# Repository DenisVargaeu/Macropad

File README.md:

# Macropad

<p align="center">

</p>

<p align="center">
  <strong>A custom 16-key macropad with OLED display and RGB LED, built around the Raspberry Pi Pico (RP2040/RP2350).</strong>
</p>

<p align="center">
  <a href="#-quick-view">Quick View</a> •
  <a href="#-features">Features</a> •
  <a href="#-hardware-specifications">Specs</a> •
  <a href="#-pinout">Pinout</a> •
  <a href="#-repository-structure">Repository</a> •
  <a href="#-getting-started">Getting Started</a> •
  <a href="#-bill-of-materials">BOM</a> •
  <a href="#-firmware">Firmware</a> •
  <a href="#-fabrication">Fabrication</a> •
  <a href="#-assembly">Assembly</a> •
  <a href="#-customization">Customization</a> •
  <a href="#-license">License</a>
</p>

---

## 📸 Quick View

| Document | Preview | Description |
|----------|---------|-------------|
| **Schematic** |  | Full schematic, all pages |
| **PCB Layout** |  | All layers (Cu, Silk, Mask, Edge) |
| **3D Model (STEP)** |  | For CAD (FreeCAD, Fusion 360, OnShape) |
| **3D Model (STL — Full)** |  | **All components** (18 MB) |
| **3D Model (STL — PCB+Pico)** |  | Board + Pico only (6 MB) — for enclosures |
| **3D Model (STL — Buttons only)** |  | Buttons only (0.4 MB) |

> 💡 **View in browser:** Click any PDF/STL link above — GitHub renders them natively. No KiCad required!

---

## ✨ Features

- **16 tactile keys** in a 4×4 matrix — direct GPIO (no matrix scanning needed)
- **0.91″ OLED display** (128×32, SSD1306, I2C) — status, layers, animations
- **RGB LED** (5 mm, common cathode) — per-key or global lighting
- **Raspberry Pi Pico / Pico 2** — RP2040 or RP2350, USB-C, BOOTSEL button accessible
- **Through-hole only** — easy hand soldering, beginner-friendly
- **Open hardware** — CERN-OHL-P-2.0 license, modify freely

---

## 🔧 Hardware Specifications

| Component | Part | Qty | Details |
|-----------|------|-----|---------|
| **MCU** | Raspberry Pi Pico / Pico 2 | 1 | RP2040 / RP2350, 133 MHz, 264 KB SRAM, 2 MB Flash |
| **Display** | ER_OLEDM0.91_1x-I2C | 1 | 0.91″, 128×32, SSD1306, I2C (EastRising/BuyDisplay) |
| **Keys** | SW_PUSH_6mm (6×6 mm tactile) | 16 | Through-hole, 4-pin (2×2 internally connected) |
| **RGB LED** | LED_D5.0mm-4_RGB_Wide_Pins | 1 | 5 mm, 4-pin common cathode (Kingbright WP154A4) |
| **Resistors** | 1/4 W axial (220–330 Ω) | 3 | Current limiting for R/G/B channels |
| **PCB** | Custom 2-layer | 1 | 1.6 mm FR4, ENIG/HASL, 100×60 mm approx. |

---

## 📌 Pinout

### Buttons — Direct GPIO (4×4 Grid)

| Key | Position | GPIO | Switch Ref | Net Name |
|-----|----------|------|------------|----------|
| 1 | Top-Left | GPIO0 | SW16 | `Net-(A1-GPIO0)` |
| 2 | | GPIO1 | SW15 | `Net-(A1-GPIO1)` |
| 3 | | GPIO2 | SW14 | `Net-(A1-GPIO2)` |
| 4 | Top-Right | GPIO3 | SW13 | `Net-(A1-GPIO3)` |
| 5 | | GPIO4 | SW8 | `Net-(A1-GPIO4)` |
| 6 | | GPIO5 | SW7 | `Net-(A1-GPIO5)` |
| 7 | | GPIO6 | SW6 | `Net-(A1-GPIO6)` |
| 8 | | GPIO7 | SW5 | `Net-(A1-GPIO7)` |
| 9 | | GPIO8 | SW4 | `Net-(A1-GPIO8)` |
| 10 | | GPIO9 | SW3 | `Net-(A1-GPIO9)` |
| 11 | | GPIO10 | SW2 | `Net-(A1-GPIO10)` |
| 12 | | GPIO11 | SW1 | `Net-(A1-GPIO11)` |
| 13 | Bottom-Left | GPIO16 | SW9 | `Net-(A1-GPIO16)` |
| 14 | | GPIO17 | SW10 | `Net-(A1-GPIO17)` |
| 15 | | GPIO18 | SW11 | `Net-(A1-GPIO18)` |
| 16 | Bottom-Right | GPIO19 | SW12 | `Net-(A1-GPIO19)` |

> **Each switch:** GPIO → GND when pressed. **Enable internal pull-ups** in firmware (`Pin.PULL_UP`).

### OLED Display (I2C)

| Signal | GPIO | Display Pin | Net |
|--------|------|-------------|-----|
| SCL | GPIO15 | Pin 3 | `Net-(A1-GPIO15)` |
| SDA | GPIO14 | Pin 4 | `Net-(A1-GPIO14)` |
| VCC | 3V3 | Pin 2 | `VCC` |
| GND | GND | Pin 1 | `GND` |

### RGB LED (Common Cathode)

| Color | Anode Net | Resistor | MCU GPIO |
|-------|-----------|----------|----------|
| **Blue** | `Net-(D2-BA)` | R1 | GPIO20 |
| **Green** | `Net-(D2-GA)` | R2 | GPIO21 |
| **Red** | `Net-(D2-RA)` | R3 | GPIO22 |
| **Cathode** | GND | — | — |

> **Resistor values:** 220 Ω (≈10 mA @ 3.3 V) or 330 Ω (≈7 mA). Adjust for brightness/uniformity.

---

## 📁 Repository Structure

```
macropad/
├── 📋 KiCad Source (editable)
│   ├── macropad.kicad_pro          # Project file
│   ├── macropad.kicad_sch          # Schematic
│   ├── macropad.kicad_pcb          # PCB layout
│   └── macropad.kicad_prl          # Local settings
│
├── 📄 Documentation (view anywhere)
│   ├── macropad-schematic.pdf      # Full schematic (PDF)
│   └── macropad-pcb.pdf            # PCB all layers (PDF)
│
├── 🎯 3D Models
│   ├── macropad-3d.step            # STEP — for CAD (FreeCAD, Fusion 360)
│   ├── macropad-3d-full.stl        # STL — ALL components (18 MB)
│   ├── macropad-pcb-pico.stl       # STL — PCB + Pico only (6 MB)
│   └── macropad-3d.stl             # STL — buttons only (0.4 MB)
│
├── 🏭 Fabrication
│   └── gerbers/                    # Gerber + drill files (gitignored)
│
├── 🔧 Utilities
│   └── export_stl.py               # FreeCAD script for STL export
│
├── 📜 LICENSE                      # CERN-OHL-P-2.0
└── 📖 README.md                    # This file
```

### Files by Category

| Category | Files | Purpose |
|----------|-------|---------|
| **KiCad Source** | `.kicad_pro`, `.kicad_sch`, `.kicad_pcb`, `.kicad_prl` | Full editable design — open in KiCad 10+ |
| **Documentation** | `macropad-schematic.pdf`, `macropad-pcb.pdf` | View schematic/PCB without KiCad |
| **3D Models** | `.step`, `.stl` (3 variants) | CAD, 3D printing, enclosure design |
| **Fabrication** | `gerbers/` (generated) | Send to PCB manufacturer |
| **License** | `LICENSE` | CERN-OHL-P-2.0 (permissive open hardware) |

---

## 🚀 Getting Started

### Prerequisites

- **KiCad 10.0+** — [Download](https://www.kicad.org/download/)
- **Raspberry Pi Pico SDK** — for C/C++ firmware
- **Soldering iron, solder, flux** — through-hole components
- **Female headers (2×20)** — for Pico module (or solder directly)

### Opening the Project

```bash
git clone https://github.com/DenisVargaeu/Macropad.git
cd Macropad
# Open in KiCad
open macropad.kicad_pro    # macOS
xdg-open macropad.kicad_pro  # Linux
start macropad.kicad_pro     # Windows
```

> **All KiCad source files are included.** No need to re-create anything — just open and edit.

---

## 📦 Bill of Materials (BOM)

| Qty | Ref | Part | Value / Spec | Notes |
|-----|-----|------|--------------|-------|
| 1 | A1 | Raspberry Pi Pico / Pico 2 | RP2040 / RP2350 | With headers or castellated |
| 1 | U1 | ER_OLEDM0.91_1x-I2C | 128×32, SSD1306, I2C | EastRising / BuyDisplay |
| 16 | SW1–SW16 | Tactile switch 6×6 mm | SW_PUSH_6mm | 4-pin, through-hole |
| 1 | D2 | RGB LED 5 mm | Common cathode, 4-pin | Kingbright WP154A4 or compatible |
| 3 | R1, R2, R3 | Resistor 1/4 W axial | 220–330 Ω | Current limiting (R/G/B) |
| 1 | — | PCB | Custom, 2-layer | Order from Gerbers |

**Approximate cost (per unit, qty 1):** ~$15–25 USD (Pico + display + switches + PCB)

---

## 🏭 Fabrication

### Option A: Use Pre-generated Gerbers (Recommended)

The `gerbers/` directory contains production-ready files:

```
gerbers/
├── macropad-F_Cu.gtl        # Front copper
├── macropad-B_Cu.gbl        # Back copper
├── macropad-F_Silkscreen.gto # Front silkscreen
├── macropad-B_Silkscreen.gbo # Back silkscreen
├── macropad-F_Mask.gts       # Front soldermask
├── macropad-B_Mask.gbs       # Back soldermask
├── macropad-Edge_Cuts.gm1    # Board outline
└── macropad.drl              # Drill file
```

Upload to **JLCPCB, PCBWay, OSH Park, AISLER**, etc.

### Option B: Generate from KiCad

1. Open `macropad.kicad_pro` in KiCad
2. `File → Fabrication Outputs → Gerbers (.gbr)`
   - Layers: F.Cu, B.Cu, F.SilkS, B.SilkS, F.Mask, B.Mask, Edge.Cuts
   - Format: Gerber X2, mm, 4.6
3. `File → Fabrication Outputs → Drill Files (.drl)`
   - Format: Excellon, mm, PTH+NPTH
4. Zip and send to fab

### Board Specifications

| Parameter | Value |
|-----------|-------|
| Layers | 2 |
| Thickness | 1.6 mm |
| Material | FR4 (standard) |
| Copper weight | 1 oz (35 µm) |
| Min track/space | 0.15 mm / 0.15 mm (6/6 mil) |
| Min drill | 0.3 mm (12 mil) |
| Surface finish | HASL or ENIG |
| Soldermask | Green (standard) |
| Silkscreen | White |

---

## 🔨 Assembly

### Component Placement

All components are **through-hole** except the Pico (castellated pads).

### Recommended Soldering Order

| Step | Components | Tips |
|------|------------|------|
| 1 | **Resistors** (R1, R2, R3) | Lowest profile first |
| 2 | **Tactile switches** (SW1–SW16) | Snap in, solder one pin, align, solder rest |
| 3 | **RGB LED** (D2) | Pin 1 = Blue anode (square pad on silkscreen) |
| 4 | **OLED display** (U1) | Pin 1 = GND (square pad); use socket if desired |
| 5 | **Female headers** for Pico | 2×20 pin, 2.54 mm pitch |
| 6 | **Insert Pico module** | Align USB-C with board cutout |

### Orientation Notes

- **Switches:** 4 pins, internally connected in pairs — orientation doesn't matter electrically
- **RGB LED:** Pin 1 (Blue) marked on silkscreen; cathode is longest pin
- **OLED:** Pin 1 = GND (square pad on footprint)
- **Pico:** USB-C faces board edge; BOOTSEL button accessible

---

## 💻 Firmware

This repository contains **hardware only**. Firmware examples below.

### Supported Frameworks

| Framework | Language | Status | Link |
|-----------|----------|--------|------|
| **Pico SDK** | C/C++ | ✅ Native | [pico-sdk](https://github.com/raspberrypi/pico-sdk) |
| **CircuitPython** | Python | ✅ Easy | [circuitpython.org](https://circuitpython.org/board/raspberry_pi_pico/) |
| **MicroPython** | Python | ✅ Official | [micropython.org](https://micropython.org/download/rp2-pico/) |
| **KMK** | Python | ✅ Keyboard-focused | [kmkfw.io](https://kmkfw.io/) |
| **QMK** | C | ✅ Community port | [qmk.fm](https://qmk.fm/) |
| **ZMK** | C/Zephyr | ⚠️ Advanced | [zmk.dev](https://zmk.dev/) |

### Minimal CircuitPython Example

```python
# macropad_firmware.py — copy to CIRCUITPY drive
import board
import digitalio
import busio
import adafruit_ssd1306
import neopixel

# ── Buttons (16 direct GPIOs with pull-ups) ──────────────────────
key_pins = [getattr(board, f"GP{i}") for i in list(range(12)) + list(range(16, 20))]
keys = [digitalio.DigitalInOut(pin) for pin in key_pins]
for k in keys:
    k.direction = digitalio.Direction.INPUT
    k.pull = digitalio.Pull.UP

# ── OLED (I2C on GP14/GP15) ──────────────────────────────────────
i2c = busio.I2C(board.GP15, board.GP14)
display = adafruit_ssd1306.SSD1306_I2C(128, 32, i2c)
display.fill(0)
display.text("Macropad Ready", 0, 0, 1)
display.show()

# ── RGB LED (PWM on GP20/21/22) ─────────────────────────────────
# Note: Requires 3 PWM channels for color mixing
import pwmio
red_pwm = pwmio.PWMOut(board.GP22, frequency=1000, duty_cycle=0)
grn_pwm = pwmio.PWMOut(board.GP21, frequency=1000, duty_cycle=0)
blu_pwm = pwmio.PWMOut(board.GP20, frequency=1000, duty_cycle=0)

def set_color(r, g, b):
    red_pwm.duty_cycle = int(r * 65535)
    grn_pwm.duty_cycle = int(g * 65535)
    blu_pwm.duty_cycle = int(b * 65535)

# ── Main loop ─────────────────────────────────────────────────────
while True:
    for i, k in enumerate(keys):
        if not k.value:  # Pressed (active low)
            print(f"Key {i+1} pressed")
            set_color(1, 0, 0)  # Red on press
        else:
            set_color(0, 0, 0)  # Off
```

### Pico SDK (C) — Button Scan Skeleton

```c
// main.c
#include "pico/stdlib.h"
#include "hardware/i2c.h"
#include "hardware/pwm.h"

#define I2C_PORT i2c1
#define SDA_PIN 14
#define SCL_PIN 15

// Button GPIOs in order
const uint btn_gpios[] = {0,1,2,3,4,5,6,7,8,9,10,11,16,17,18,19};
const uint NUM_BTNS = 16;

// RGB PWM pins
const uint RED_PIN = 22, GRN_PIN = 21, BLU_PIN = 20;

int main() {
    stdio_init_all();

    // Buttons with pull-ups
    for (int i = 0; i < NUM_BTNS; i++) {
        gpio_init(btn_gpios[i]);
        gpio_set_dir(btn_gpios[i], GPIO_IN);
        gpio_pull_up(btn_gpios[i]);
    }

    // I2C for OLED
    i2c_init(I2C_PORT, 400000);
    gpio_set_function(SDA_PIN, GPIO_FUNC_I2C);
    gpio_set_function(SCL_PIN, GPIO_FUNC_I2C);
    gpio_pull_up(SDA_PIN); gpio_pull_up(SCL_PIN);

    // PWM for RGB
    for (uint pin : {RED_PIN, GRN_PIN, BLU_PIN}) {
        gpio_set_function(pin, GPIO_FUNC_PWM);
        uint slice = pwm_gpio_to_slice_num(pin);
        pwm_set_wrap(slice, 255);
        pwm_set_enabled(slice, true);
    }

    while (true) {
        for (int i = 0; i < NUM_BTNS; i++) {
            if (!gpio_get(btn_gpios[i])) {
                printf("Key %d pressed\n", i+1);
                pwm_set_gpio_level(RED_PIN, 255);
            } else {
                pwm_set_gpio_level(RED_PIN, 0);
            }
        }
        sleep_ms(10);
    }
}
```

### KMK (Python Keyboard Firmware)

```python
# kmk_config.py
import board
from kmk.keys import KC
from kmk.kmk_keyboard import KMKKeyboard
from kmk.scanners import DiodeOrientation
from kmk.modules.rgb import RGB

keyboard = KMKKeyboard()

# Direct pin matrix (no diodes needed with pull-ups)
keyboard.col_pins = (
    board.GP0, board.GP1, board.GP2, board.GP3,
    board.GP4, board.GP5, board.GP6, board.GP7,
    board.GP8, board.GP9, board.GP10, board.GP11,
    board.GP16, board.GP17, board.GP18, board.GP19,
)
keyboard.row_pins = (board.GND,)  # Single row to GND
keyboard.diode_orientation = DiodeOrientation.COL2ROW

# RGB on GP20/21/22
rgb = RGB(pixel_pin=board.GP20, num_pixels=1, val_default=50)
keyboard.modules.append(rgb)

# Keymap
keyboard.keymap = [
    [KC.N1, KC.N2, KC.N3, KC.N4,
     KC.N5, KC.N6, KC.N7, KC.N8,
     KC.N9, KC.A, KC.B, KC.C,
     KC.D, KC.E, KC.F, KC.G]
]

if __name__ == '__main__':
    keyboard.go()
```

---

## 🎨 Customization

| Change | How |
|--------|-----|
| **Key layout** | Edit switch positions in `macropad.kicad_pcb` (Footprint Properties → Position) |
| **Display** | Replace `Display:ER_OLEDM0.91_1x-I2C` footprint with any I2C OLED (SSD1306, SH1106) |
| **RGB LED** | Swap `LED_THT:LED_D5.0mm-4_RGB_Wide_Pins` for common-anode or different package |
| **MCU** | Footprint `Module:RaspberryPi_Pico_Common_Unspecified` supports Pico, Pico W, Pico 2 |
| **Add per-key LEDs** | Add 16× SK6812MINI-E or WS2812B footprints + series resistors |
| **Rotary encoder** | Add EC11 footprint + 2 GPIOs (e.g., GP26/GP27) |

---

## 🐛 Known Issues / Errata

| Issue | Status | Workaround |
|-------|--------|------------|
| OLED 3D model missing in KiCad library | ⚠️ Known | STL/STEP exports show placeholder; download model from BuyDisplay |
| Pico USB-C cutout may need filing | ⚠️ Minor | Test fit before soldering headers |
| RGB LED pins tight for 5 mm wide-pin | ⚠️ Minor | Slightly bend leads or use standard 2.54 mm spacing LED |

---

## 📝 Changelog

| Version | Date | Changes |
|---------|------|---------|
| **v1.0.0** | 2026-11-08 | Initial release — schematic, PCB, 3D models, documentation |

---

## 🤝 Contributing

1. Fork the repository
2. Create a feature branch: `git checkout -b feature/amazing-idea`
3. Make changes in **KiCad 10+**
4. Run DRC: `Inspect → Design Rules Checker` (must pass with 0 errors)
5. Update README if needed
6. Submit PR with clear description and screenshots

### Development Setup

```bash
# Install KiCad 10+ (Ubuntu/Debian)
sudo add-apt-repository ppa:kicad/kicad-10.0-releases
sudo apt update && sudo apt install kicad

# Or download from kicad.org
```

---

## 📚 Resources

- **Raspberry Pi Pico Datasheet** — <https://datasheets.raspberrypi.com/pico/pico-datasheet.pdf>
- **Pico 2 (RP2350) Datasheet** — <https://datasheets.raspberrypi.com/pico/pico-2-datasheet.pdf>
- **SSD1306 OLED (ER-OLEDM0.91-1)** — <https://www.buydisplay.com/download/manual/ER-OLEDM0.91-1_Datasheet.pdf>
- **Kingbright WP154A4 RGB LED** — <https://www.kingbright.com/attachments/file/psearch/000/00/00/L-154A4SUREQBFZGEW(Ver.11A).pdf>
- **KiCad 10 Documentation** — <https://docs.kicad.org/10.0/>
- **Pico SDK** — <https://github.com/raspberrypi/pico-sdk>
- **CircuitPython for Pico** — <https://circuitpython.org/board/raspberry_pi_pico/>

---

## ⚖️ License

This hardware design is released under the **CERN Open Hardware Licence Version 2 - Permissive (CERN-OHL-P-2.0)**.

```
Copyright (c) 2026 Denis Varga

Licensed under the CERN-OHL-P-2.0 or any later version.
You may redistribute and modify this design under the terms of the CERN-OHL-P-2.0.
This design is distributed WITHOUT ANY EXPRESS OR IMPLIED WARRANTY.
See the CERN-OHL-P-2.0 for details.
```

**SPDX-License-Identifier:** `CERN-OHL-P-2.0`

Full license text: <https://ohwr.org/cern_ohl_p_2_0.txt> | <https://opensource.org/licenses/CERN-OHL-P-2.0>

---

<p align="center">
  <strong>Designed with ❤️ in KiCad 10.0</strong><br>
  Made for makers, by makers
</p>

<p align="center">
  <a href="https://github.com/DenisVargaeu/Macropad">⭐ Star this repo</a> •
  <a href="https://github.com/DenisVargaeu/Macropad/issues">🐛 Report bug</a> •
  <a href="https://github.com/DenisVargaeu/Macropad/discussions">💬 Discuss</a>
</p>

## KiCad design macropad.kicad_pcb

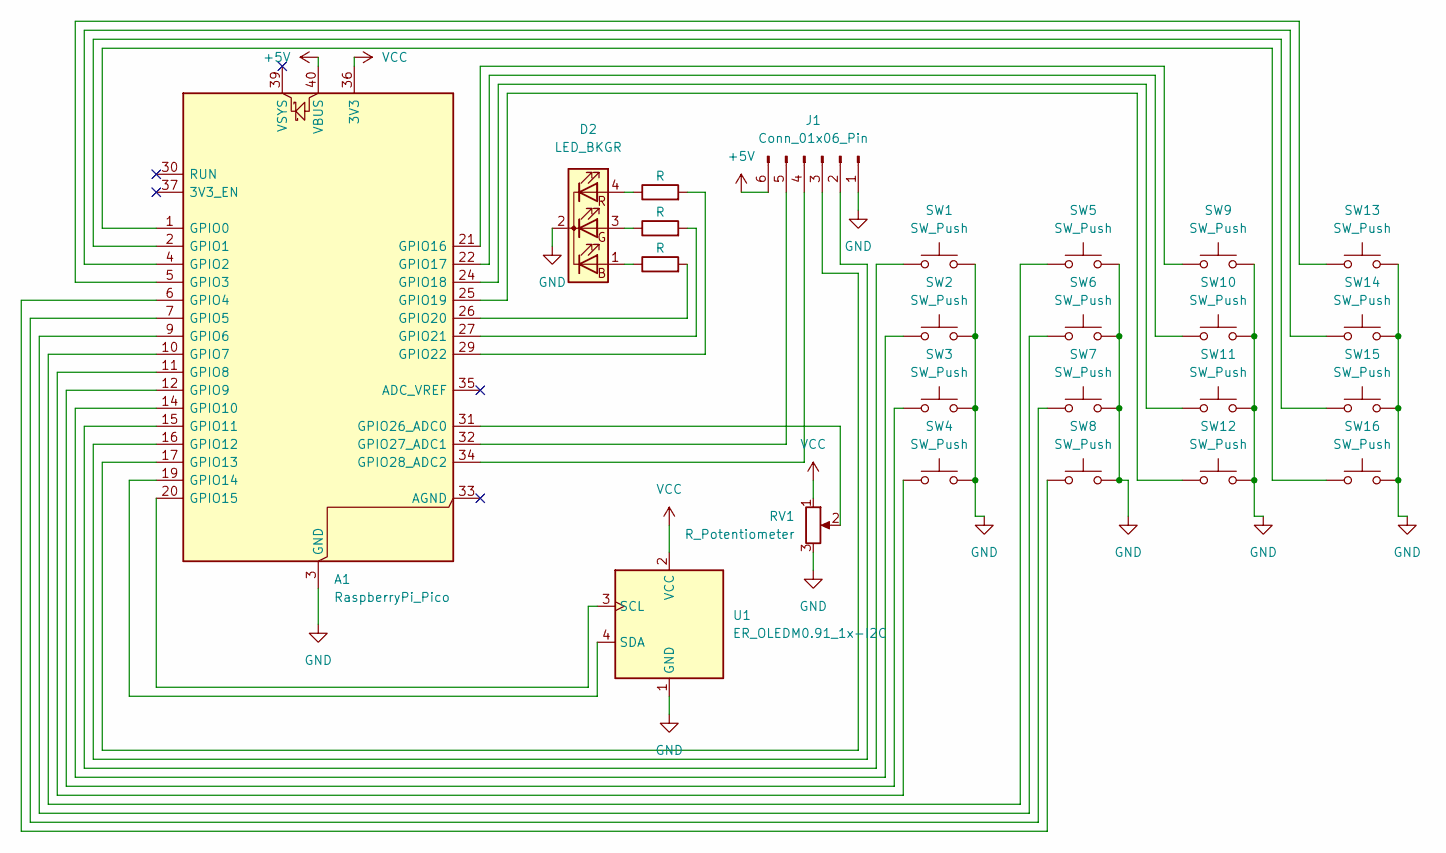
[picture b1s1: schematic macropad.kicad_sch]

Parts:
A1: RaspberryPi_Pico; RaspberryPi_Pico_Common_Unspecified
D2: LED_BKGR; LED_D5.0mm-4_RGB_Wide_Pins
J1: Conn_01x06_Pin
R1, R2, R3: R; R_Axial_DIN0207_L6.3mm_D2.5mm_P7.62mm_Horizontal
RV1: R_Potentiometer; Potentiometer_Alps_RK09K_Single_Vertical
SW1, SW2, SW3, SW4, SW5, SW6, SW7, SW8, SW9, SW10, SW11, SW12, SW13, SW14, SW15, SW16: SW_Push; SW_PUSH_6mm
U1: ER_OLEDM0.91_1x-I2C

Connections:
+5V: A1.40 (VBUS), J1.6
GND: A1.3 (GND), A1.8 (GND), A1.13 (GND), A1.18 (GND), A1.23 (GND), A1.28 (GND), A1.38 (GND), D2.2 (K), J1.1, RV1.3, SW1.2, SW2.2, SW3.2, SW4.2, SW5.2, SW6.2, SW7.2, SW8.2, SW9.2, SW10.2, SW11.2, SW12.2, SW13.2, SW14.2, SW15.2, SW16.2, U1.1 (GND)
unnamed: A1.1 (GPIO0), SW16.1
unnamed: A1.2 (GPIO1), SW15.1
unnamed: A1.4 (GPIO2), SW14.1
unnamed: A1.5 (GPIO3), SW13.1
unnamed: A1.6 (GPIO4), SW8.1
unnamed: A1.7 (GPIO5), SW7.1
unnamed: A1.9 (GPIO6), SW6.1
unnamed: A1.10 (GPIO7), SW5.1
unnamed: A1.11 (GPIO8), SW4.1
unnamed: A1.12 (GPIO9), SW3.1
unnamed: A1.14 (GPIO10), SW2.1
unnamed: A1.15 (GPIO11), SW1.1
unnamed: A1.16 (GPIO12), J1.2
unnamed: A1.17 (GPIO13), J1.3
unnamed: A1.19 (GPIO14), U1.4 (SDA)
unnamed: A1.20 (GPIO15), U1.3 (SCL)
unnamed: A1.21 (GPIO16), SW9.1
unnamed: A1.22 (GPIO17), SW10.1
unnamed: A1.24 (GPIO18), SW11.1
unnamed: A1.25 (GPIO19), SW12.1
unnamed: A1.26 (GPIO20), R1.2
unnamed: A1.27 (GPIO21), R2.2
unnamed: A1.29 (GPIO22), R3.2
unnamed: A1.31 (GPIO26_ADC0), RV1.2
unnamed: A1.32 (GPIO27_ADC1), J1.5
unnamed: A1.34 (GPIO28_ADC2), J1.4
unnamed: D2.1 (BA), R1.1
unnamed: D2.3 (GA), R2.1
unnamed: D2.4 (RA), R3.1
VCC: A1.36 (3V3), RV1.1, U1.2 (VCC)

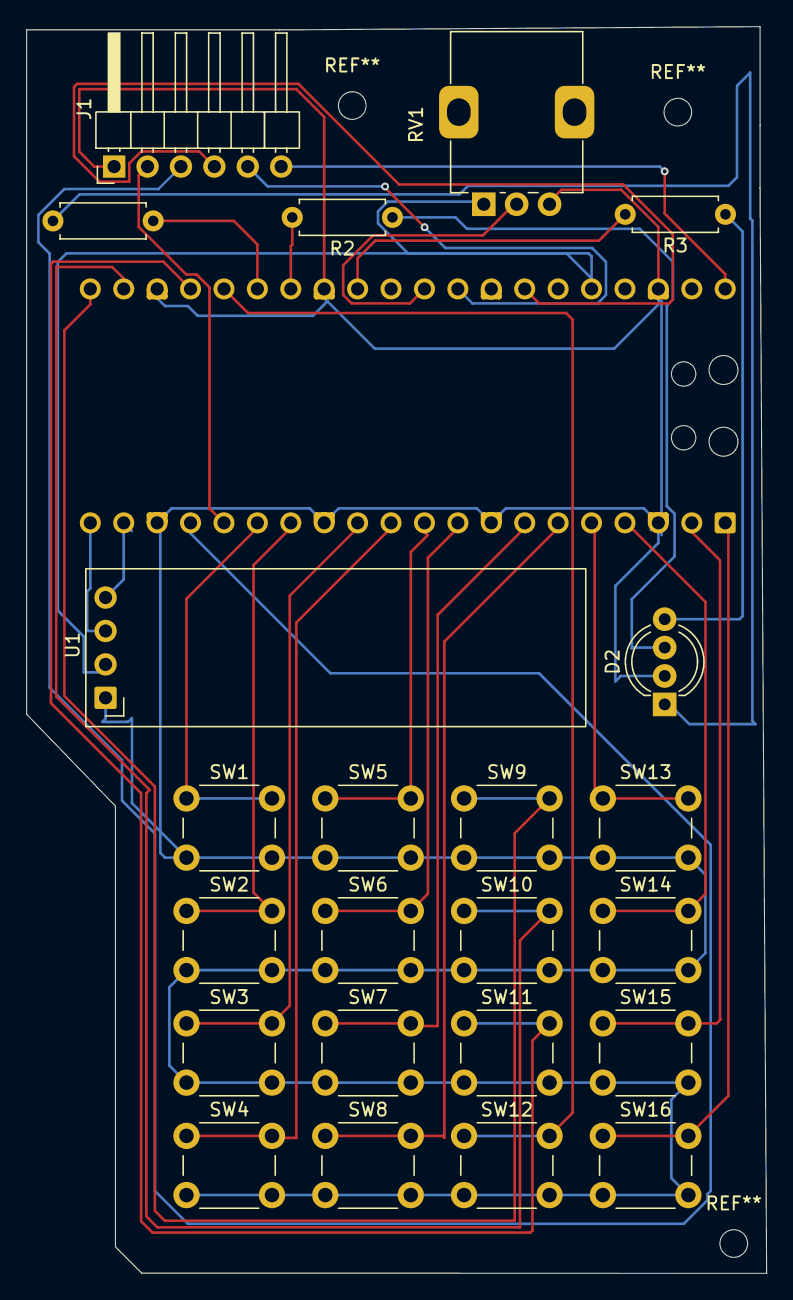
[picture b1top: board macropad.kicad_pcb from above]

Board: 2 copper layers, 56.2 x 94.8 mm, 24 parts (1 on the bottom side), 32 nets.
